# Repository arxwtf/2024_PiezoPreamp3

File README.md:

# Piezo Preamp with Baxandall Tone Control and Battery Indicator

A simple preamp to be used for e.g. guitar piezo (contact) microphones. 

Created in KiCAD v8 and LTSpice.

### [**User manual**](Arx_PiezoPreamp-User_Manual.pdf) | [**Detailed info**](https://arx.wtf/blog/3-piezo-preamp) | [**Enclosure**](https://github.com/arxwtf/2024_PiezoPreamp3_Enclosure)

## Main circuit blocks

### Charge amplifier for piezo 

Basically an integrator circuit. Provides low-impedance input. The gain is adjustable and depends on the input piezo capacitance. In my measurements, piezo discs have following capacitances:

- small disc (15mm diameter): ~7-10nF
- medium disc (27mm diameter): ~16-22nF
- large disc (35mm diameter): ~37-40nF

But I've also seen mentions of piezo discs with <10nF capacitance. Connecting multiple piezo discs in parallel increases the capacitance, so the maximum piezo capacitance can be in order of ~100nF or so.

The gain of the charge amp is then set by the ration of piezo capacitance to charge amp feedback capacitance. The **gain slide switch** is used to select from these feedback capacitances:

- 1nF
- 5.7nF
- 10.4nF
- 23nF

Input is protected by ESD bidirectional diode.

OPA145 is the opamp of choice because of these characteristics:
- JFET input stage, which means low input bias and offset current - critical for a charge amplifier
- low quiescent current (0.7mA max) for battery operation
- acceptable input voltage noise density (7nV/rtHz)
- good current noise density (0.8fA/rtHz)
- sufficient slew rate for audio (20V/us)
- sufficient GBW (5.5MHz)
- single supply voltage range 4.5V - 36V
- output voltage swing (V- +0.3, V+ -0.3)

Opamp also unfortunately seems to have bias current cancellation, which might introduce more current noise - this has to be determined by measurement. The same opamp is also used for Baxandall tone control section. Two single OPA145 components are used instead of dual OPA2145 package because it's easier to route, minimizes crosstalk and improves power dissipation (less heat). This increases the price, of course.

### High-pass filter with HPF switch

The charge amp is followed by a simple first-order high-pass filter with switchable cutoff frequency:
- 0Hz 
- 50Hz
- 77Hz
- 113Hz

The cutoff frequency is selectable by **HPF slide switch**.

### Baxandall tone control with Center switch

Bass and treble can be adjusted independently by **Bass pot** and **Treble pot** in the ranges of +-10dB. The center frequency is switchable by **Center slide switch**:

- 350Hz
- 600Hz
- 1kHz

Output audio is routed through **Volume pot** and protected by ESD bidirectional diode.

### Power-on LED and battery indicator
The power-on LED can work in two modes, switchable by LED mode switch:
- always on (switch left)
- "battery indication mode" (switch right)

**Battery indication mode (BI)** causes the LED to flash briefly when the circuit is switched on (by inserting mono plug to output jack + moving the power-on switch to the right). The longer the flash, the lower the battery voltage (remaining capacity). Under certain threshold, the LED will stay on permanentnly, signalling the need for replacement. This **BI threshold** is adjustable by on-board trimmer pot and needs to be determined by voltmeter measurement.

### Power supply
Designed for 9V batteries or DC pedal power supplies, but should theoretically be able to work properly with up to 18V DC.

Power enters the PCB by means of standardi 5.5/2.1mm DC IN connector with switch to disconnect internal 9V battery.

Contains ESD protection (bidirectional diode), MOSFET reverse polarity protection (with Zener gate protection and CLR) and input pi filter.

### OFF/ON switch with true bypass
The power-on switch works as a true bypass switch in its left position. The device is switched on by moving the switch to the right and insertin a **mono** male audio plug into the output jack.

## Simulation: /ltspice folder
LTSpice simulations (transient, AC, noise, stability) and some graphs are available in `ltspice/` folder.

## /library folder
Folder containing all 3rd symbols, footprints and 3D models used in the project. Other than that, only standard KiCAD symbols are used (opamps, ).

## /production folder
Contains gerbers, position files, BOM file, screenshot of JLC settings etc.

## /resources folder
Contains some additional resources, inspiration and schematics used during development.

## /schematics folder
Contains schematic sheets plotted from KiCAD, individually as .png and in one file as .pdf.

## Known problems
- when the circuit is turned ON or OFF (by the power-on switch and inserting of cable into AUDIO OUT jack), it might produce a strong voltage transient (a loud "pop"). Be careful when you're using it with sensitive equipment downstream.

- battery spring (used only for grounding) is too close to the PCB edge. This creates unnecessary force between the PCB and the enclosure wall. The spring can be shortened, or not used at all.

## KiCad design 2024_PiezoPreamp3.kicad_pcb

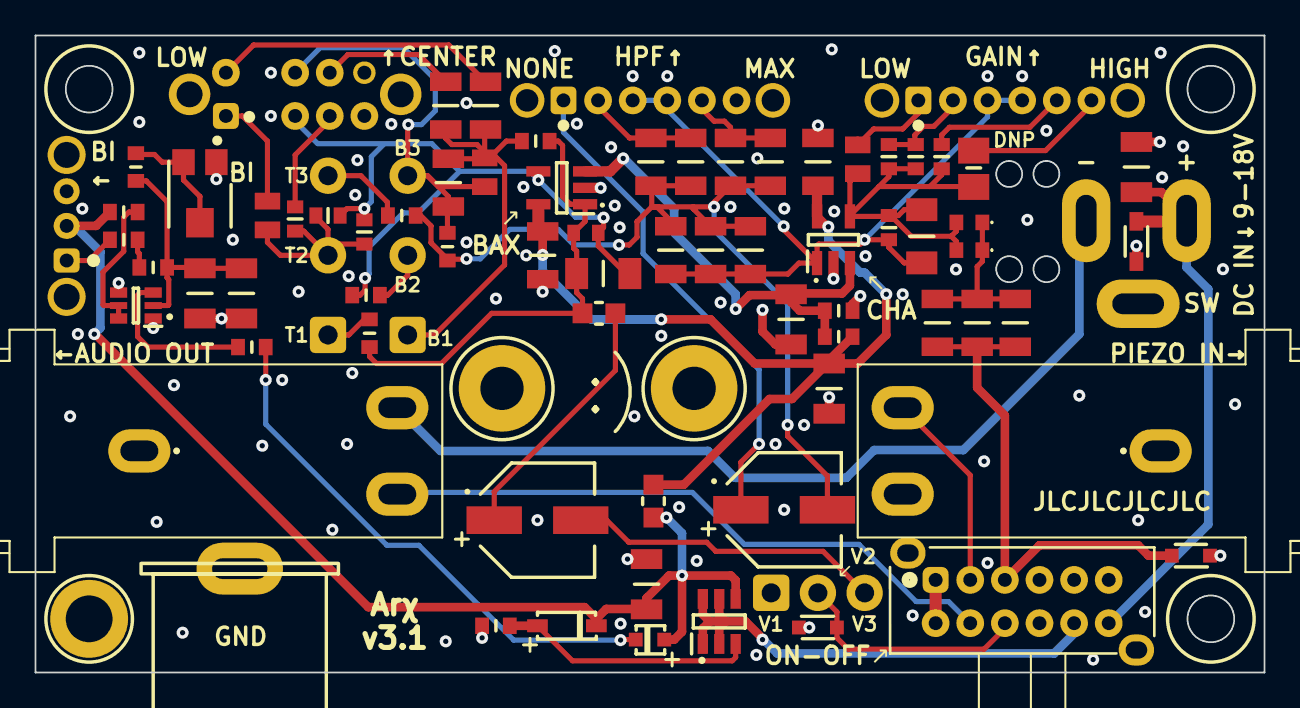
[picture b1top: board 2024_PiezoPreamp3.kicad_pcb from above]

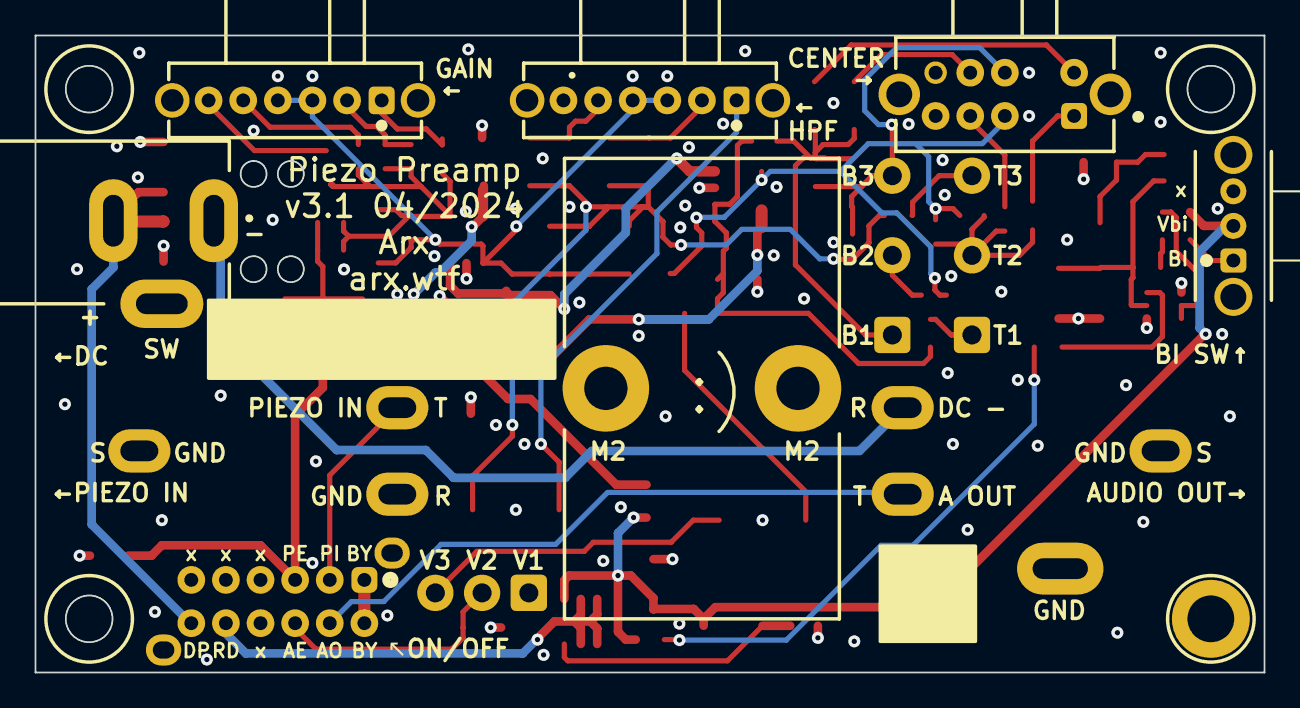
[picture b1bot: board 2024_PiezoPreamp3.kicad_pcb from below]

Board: 4 copper layers, 71.0 x 36.8 mm, 94 parts (6 on the bottom side), 45 nets.

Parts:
Bass: Bass; pot_R16148-1A-1_FabOnly
Batt1, Batt2, Batt3, Batt4: FreeHole_1.5mm
C101, C102, C103: 220n; GRM31C5C1H224JE02L
C104: 100p; cap_CL10C101JB8NNNC
C105: 100u 50V; EEEFTH101XAP
C201, C202, C203, C204, C301, C302: 22u; cap_CL31A226KAHNNNE
C205, C206: 100n; GRM31C5C1H104JA01L
Cb101, Cb104: 68n; GRM31C5C1H683JA01L
Cb102: 22n; GRM21B5C1H223JA01L
Cb103: 100n; GRM31C5C1H104JA01L
Cf101: 1n; GRM1885C1H102JA01D
Cf102: 22n; GRM21B5C1H223JA01L
Cf103, Cf104, Cf105: 4n7; GRM1885C1H472JA01D
Cf106: 1n; cap_SMD_DNP
Chp101, Chp108: 68n; GRM31C5C1H683JA01L
Chp102, Chp103, Chp105, Chp106: 220n; GRM31C5C1H224JE02L
Chp104: 100u 50V; EEEFTH101XAP
Chp107: 100n; GRM31C5C1H104JA01L
Ct101, Ct102, Ct104: 4n7; GRM1885C1H472JA01D
Ct103: 22n; GRM21B5C1H223JA01L
D101, D102: 12V 1pF; CDSOD323-T12LC
D201: 20V 15pF; D20V0L1B2WS-7
D202: DDZ12B-7
D301: Red 100mcd/120°/2mA; APT1608LSECK_J3-PRV
H101: Bass 1; FreePad_1.1mm_2.1mm_rect
H102: Bass 2; FreePad_1.1mm_2.1mm
H103: Bass 3; FreePad_1.1mm_2.1mm
H104: Treble 1; FreePad_1.1mm_2.1mm_rect
H105: Treble 2; FreePad_1.1mm_2.1mm
H106: Treble 3; FreePad_1.1mm_2.1mm
H107: Volume 1; FreePad_1.1mm_2.1mm_rect
H108: Volume 2; FreePad_1.1mm_2.1mm
H109: Volume 3; FreePad_1.1mm_2.1mm
H401: M2.5 MountingHole_Pad; MountingHole_2.7mm_M2.5_ISO14580_Pad
H402, H403, H404: M2.5 MountingHole; MountingHole_2.7mm_M2.5_ISO14580
H422: 9V battery holder; KEYSTONE-71
J101, J102: 6.3mm stereo; CUI_SJ-63053A
J201: DC IN 5.5/2.1mm; 694106301002
J401: Spring Contact; KEYSTONE-5201
R101, R102: 150R; ERA-3AEB151V
R103, R303: 3k9; RT0603FRE073K9L
R104: 10M; MCA1206MD1005BP100
R105, R202: 100R; ERA-6AEB101V
R201, R305: 10k; RT0603BRD0710KL
R203, R204, R301, R302, R304: 47k; RT0603FRD0747KL
RV301: trim B10k; trimpot_TC33X-2-103E
Rb101, Rb102: 3k9; RT0603FRE073K9L
Rf101: 10M; MCA1206MD1005BP100
Rt101, Rt102: 2k2; RT0603DRD072K2L
S101, S102: SK14D01G6; sw_SK14D01G6
S103: 0S203011MA2QP1; sw_0S203011MA2QP1
S201: EG4208A
S301: OS102011MA1QN1
Treble: Treble; pot_R16148-1A-1_FabOnly
U101, U102: OPA145; OPA145IDBVR
U201: ZXMP3A17E6TA
U301: BC847BS,115; bjt_BC847BS_115
Volume: Volume; pot_R16148-1A-1_FabOnly

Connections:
/1-ChargeAmpAndEQ/BASS_1: Cb101.2, Cb102.1, Cb103.2, Cb104.2, H101.1, Rb102.1
/1-ChargeAmpAndEQ/BASS_2: H102.1, R103.1
/1-ChargeAmpAndEQ/BASS_3: Cb101.1, Cb102.2, H103.1, Rb101.2, S103.6 (1_C)
/1-ChargeAmpAndEQ/BAX_A_INV: C104.1, Ct101.1, Ct102.1, R103.2, R104.2, S103.2 (2_C), U102.4 (-)
/1-ChargeAmpAndEQ/BAX_A_OUT: C104.2, R104.1, R105.2, Rb102.2, Rt102.2, U102.1
/1-ChargeAmpAndEQ/BAX_IN: Chp101.2, Chp102.2, Chp103.2, Chp104.2, Chp105.1, Chp106.1, Chp107.2, Chp108.2, Rb101.1, Rt101.1
/1-ChargeAmpAndEQ/CH_A_INV: Cf101.1, Cf102.1, Cf103.1, Cf104.1, Cf105.1, Cf106.1, R101.2, R102.2, Rf101.1, U101.4 (-)
/1-ChargeAmpAndEQ/CH_A_OUT: Cf101.2, Chp101.1, Chp102.1, Chp103.1, Rf101.2, S101.3 (C1), S101.4 (C2), S102.3 (C1), S102.4 (C2), U101.1
/1-ChargeAmpAndEQ/CIN_RIN: C101.2, C102.2, C103.2, R101.1, R102.1
/1-ChargeAmpAndEQ/C_SW_1: Ct103.2, S103.1 (2_1)
/1-ChargeAmpAndEQ/C_SW_2: Ct104.2, S103.3 (2_2)
/1-ChargeAmpAndEQ/C_SW_5: Cb103.1, S103.5 (1_1)
/1-ChargeAmpAndEQ/C_SW_7: Cb104.1, S103.7 (1_2)
/1-ChargeAmpAndEQ/G_SW_1: Cf102.2, S101.1
/1-ChargeAmpAndEQ/G_SW_2: Cf103.2, Cf104.2, S101.2
/1-ChargeAmpAndEQ/G_SW_5: Cf105.2, S101.5 (3)
/1-ChargeAmpAndEQ/G_SW_6: Cf106.2, S101.6 (4)
/1-ChargeAmpAndEQ/HPF_SW_1: Chp104.1, S102.1
/1-ChargeAmpAndEQ/HPF_SW_2: Chp105.2, Chp106.2, S102.2
/1-ChargeAmpAndEQ/HPF_SW_3: Chp107.1, Chp108.1, S102.5 (3)
/1-ChargeAmpAndEQ/ROUT_COUT: C105.1, R105.1
/1-ChargeAmpAndEQ/TREB_1: H104.1, Rt102.1
/1-ChargeAmpAndEQ/TREB_2: Ct101.2, Ct102.2, Ct103.1, Ct104.1, H105.1
/1-ChargeAmpAndEQ/TREB_3: H106.1, Rt101.2
/1-ChargeAmpAndEQ/VOL_3: C105.2, H109.1
/2-Power/BYPASS: S201.1, S201.7
/2-Power/DC_IN_POS: C201.2, D201.2 (A2), J201.2 (SLEEVE), S201.12
/2-Power/RP_DRAIN: S201.11, U201.1, U201.2, U201.5, U201.6
/2-Power/RP_GATE: D202.2 (A), R201.1, U201.3
/3-BatteryIndicator/BI_B1: C301.2, C302.2, R302.2, R303.1, U301.2 (B1)
/3-BatteryIndicator/BI_C1_B2: R304.2, U301.5 (B2), U301.6 (C1)
/3-BatteryIndicator/BI_C2: R305.2, U301.3 (C2)
/3-BatteryIndicator/BI_R: R301.2, R302.1
/3-BatteryIndicator/BI_SW: R301.1, S301.1
/3-BatteryIndicator/LED_K: D301.1 (K), R305.1
/3-BatteryIndicator/TRIM_BI_3: R303.2, RV301.2, RV301.3
AUDIO_ESD: D102.2 (A2), H108.1, S201.9
AUDIO_OUT: J102.2, S201.8
DC_IN_NEG: J102.3, J201.1 (CENTER)
GND: C201.1, C202.1, C203.1, C204.1, C205.1, C206.1, C301.1, C302.1, D101.1 (A1), D102.1 (A1), D201.1 (A1), H107.1, H401.1, J101.1, J101.3, J102.1, J401.1, R201.2, R204.2, RV301.1, U101.2 (V-), U102.2 (V-), U301.1 (E1), U301.4 (E2)
PIEZO_ESD: C101.1, C102.1, C103.1, D101.2 (A2), S201.3
PIEZO_IN: J101.2, S201.2
VS: C203.2, C205.2, C206.2, R202.1, R203.1, U101.5 (V+), U102.5 (V+)
Vbi: C202.2, D202.1 (K), D301.2 (A), R202.2, R304.1, S301.2, U201.4
Vbias: C204.2, R203.2, R204.1, U101.3 (+), U102.3 (+)

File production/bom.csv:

Designator,Footprint,Quantity,Value,LCSC Part #
"C101, C102, C103, Chp102, Chp103, Chp105, Chp106",GRM31C5C1H224JE02L,7,220n,C464977
C104,cap_CL10C101JB8NNNC,1,100p,C14858
"C105, Chp104",EEEFTH101XAP,2,100u 50V,C165974 
"C201, C202, C203, C204, C301, C302",cap_CL31A226KAHNNNE,6,22u,C12891
"C205, C206, Cb103, Chp107",GRM31C5C1H104JA01L,4,100n,C97946
"Cb101, Cb104, Chp101, Chp108",GRM31C5C1H683JA01L,4,68n,C77084
"Cb102, Cf102, Ct103",GRM21B5C1H223JA01L,3,22n,C77069
Cf101,GRM1885C1H102JA01D,1,1n,C77026
"Cf103, Cf104, Cf105, Ct101, Ct102, Ct104",GRM1885C1H472JA01D,6,4n7,C85980
"D101, D102",CDSOD323-T12LC,2,12V 1pF,C911368
D201,D20V0L1B2WS-7,1,20V 15pF,C507921
D202,DDZ12B-7,1,DDZ12B-7,C2760568
D301,APT1608LSECK_J3-PRV,1,Red 100mcd/120°/2mA,C5357909
H422,KEYSTONE-71,1,9V battery holder,-
"J101, J102",CUI_SJ-63053A,2,6.3mm stereo,-
J201,694106301002,1,DC IN 5.5/2.1mm,-
J401,KEYSTONE-5201,1,Spring Contact,-
"R101, R102",ERA-3AEB151V,2,150R,C543626
"R103, R303, Rb101, Rb102",RT0603FRE073K9L,4,3k9,C863790
"R104, Rf101",MCA1206MD1005BP100,2,10M,C4259100
"R105, R202",ERA-6AEB101V,2,100R,C445646
"R201, R305",RT0603BRD0710KL,2,10k,C95204
"R203, R204, R301, R302, R304",RT0603FRD0747KL,5,47k,C728633
RV301,trimpot_TC33X-2-103E,1,trim B10k,C719176
"Rt101, Rt102",RT0603DRD072K2L,2,2k2,C705970
"S101, S102",sw_SK14D01G6,2,SK14D01G6,
S103,sw_0S203011MA2QP1,1,0S203011MA2QP1,
S201,EG4208A,1,EG4208A,-
S301,OS102011MA1QN1,1,OS102011MA1QN1,-
"U101, U102",OPA145IDBVR,2,OPA145,C2058624
U201,ZXMP3A17E6TA,1,ZXMP3A17E6TA,C154715
U301,bjt_BC847BS_115,1,"BC847BS,115",C8653

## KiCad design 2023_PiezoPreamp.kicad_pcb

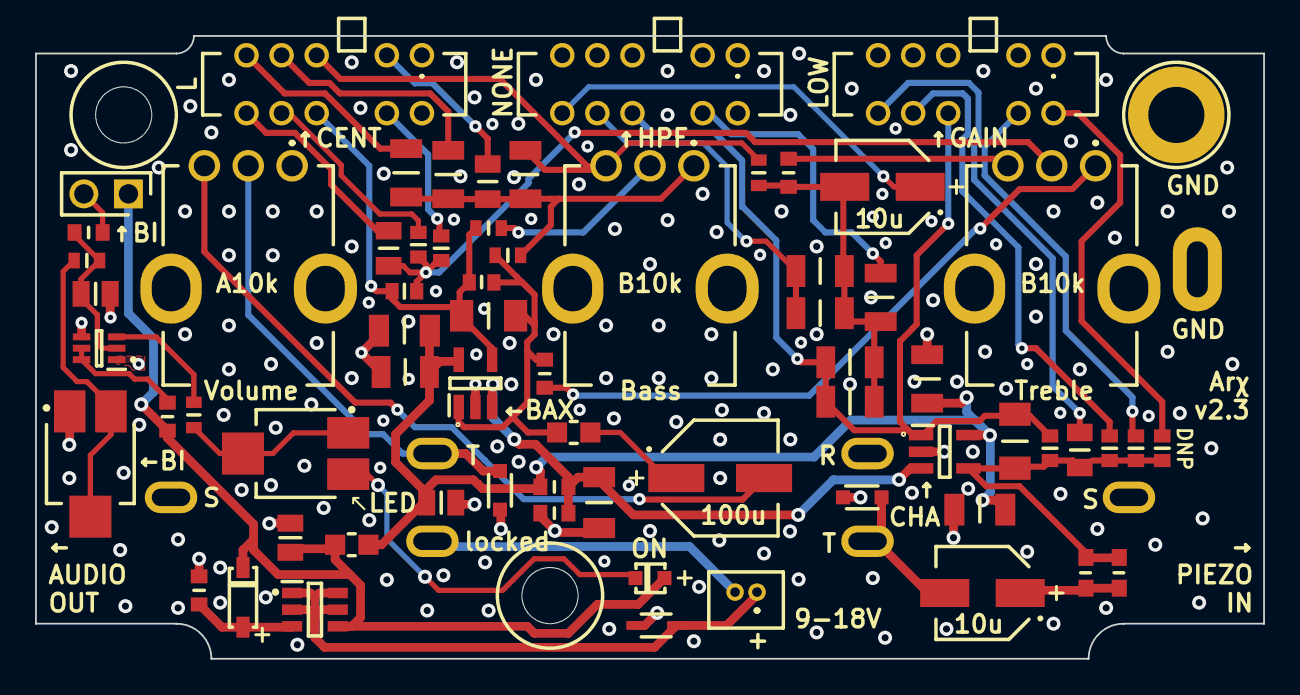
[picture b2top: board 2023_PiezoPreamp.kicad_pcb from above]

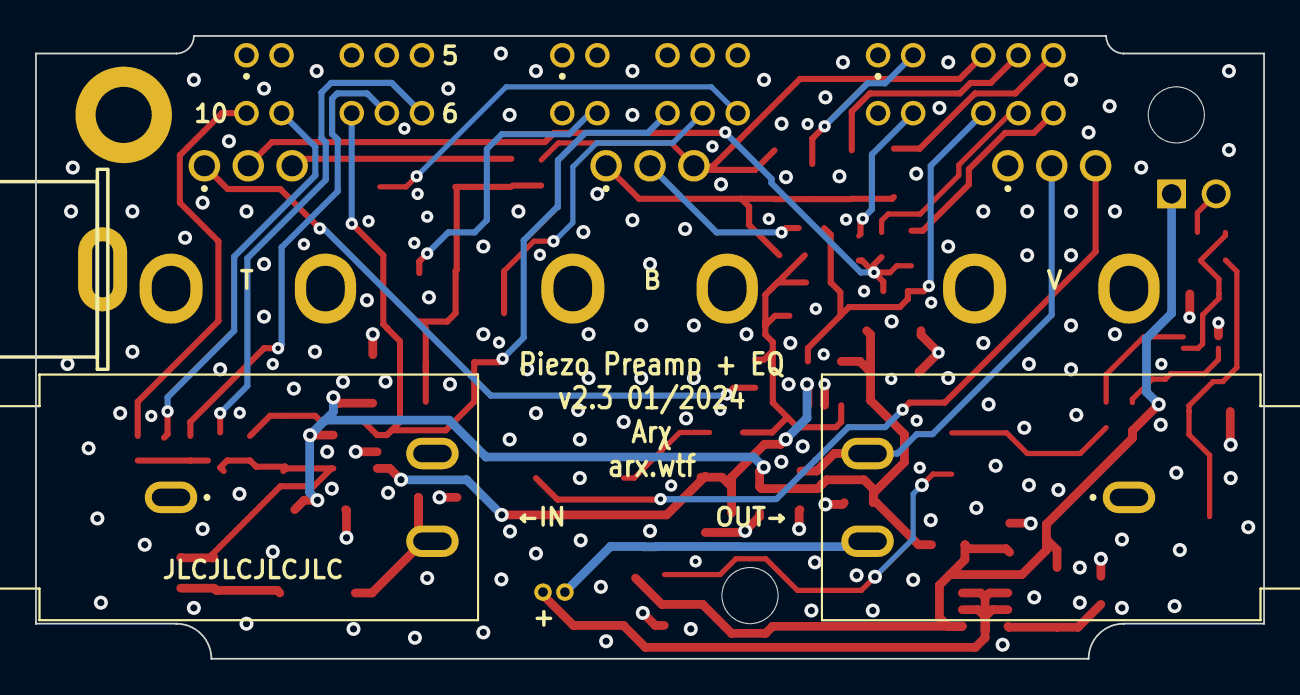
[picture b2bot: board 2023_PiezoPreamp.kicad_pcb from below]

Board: 4 copper layers, 70.0 x 35.5 mm, 73 parts (3 on the bottom side), 43 nets.

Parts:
C101: 10u 50V; EEEFK1H100UR
C102: 100p; GRM1885C1H101JA01D
C103: 100u 50V; EEEFTH101XAP
C201, C202, C301: 22u; GRM21BR61E226ME44L
C203, C205, C207: 10u; C3216X5R1H106K160AB
C204, C206: 100n; GRM31C5C2A104JA01L
Cb101, Cb103: 68n; GRM31C5C1H683JA01L
Cb102: 100n; GRM31C5C2A104JA01L
Cb104: 22n; CGA4J2C0G1H223J125AA
Cf101, Cf105: 1n; GRM1885C1H102JA01D
Cf102: 22n; CGA4J2C0G1H223J125AA
Cf103: 10n; GRM1885C1H103JA01D
Cf104: 4n7; GRM1885C1H472JA01D
Chp101: 68n; GRM31C5C1H683JA01L
Chp102, Chp104, Chp105, Chp106: 220n; GRM31C5C1H224JE02L
Chp103: 10u 50V; EEEFK1H100UR
Ct101, Ct103: 6n8; GRM1885C1H682JA01D
Ct102: 22n; CGA4J2C0G1H223J125AA
Ct104: 4n7; GRM1885C1H472JA01D
D101, D102: 12V 1pF; CDSOD323-T12LC
D201: 20V 15pF; D20V0L1B2WS-7
D202: DDZ12B-7
D301: Red 100mcd/120°/2mA; APT1608LSECK_J3-PRV
H401: M3 MountingHole_Pad; MountingHole_3.2mm_M3_ISO14580_Pad
H402, H403: M3 MountingHole; MountingHole_3.2mm_M3_ISO14580
J101, J102: 6.3mm stereo; CUI_SJ-63053A
J201: Molex PicoBlade; 53047-0210
J301: 2.54mm header; 77311-818-02
J401: Spring Contact; KEYSTONE-5201
R101, R102: 150R; RT0603BRD07150RL_UL-M
R103, R302, R304: 3k9; ERA-3AEB392V
R104: 10M; MCA1206MD1005BP100
R105, R202: 100R; ERA-6AEB101V
R201: 10k; RT0603BRD0710KL
R203, R204, R303: 47k; RT0603BRD0747KL
R301: 100k; RT0603BRD07100KL
RV101, RV102: B10k; PTV09A-4020F-A103
RV103: A10k; PTV09A-4020F-A103
RV301, RV302: trim B10k; ST-4ETB103
Rb101, Rb102: 3k9; ERA-3AEB392V
Rf101: 10M; MCA1206MD1005BP100
Rt101, Rt102: 2k2; RT0603DRD072K2L
S101, S102, S103: SSSS224100
U101, U102: OPA145; OPA145IDBVR
U201: ZXMP3A17E6TA
U301: MMDT2222A-7-F

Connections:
/1-ChargeAmpAndEQ/AUDIO_OUT: D102.2 (A2), J102.2, RV103.2
/1-ChargeAmpAndEQ/BAX_A_INV: C102.1, Ct101.1, R103.2, R104.2, S103.8, U102.4 (-)
/1-ChargeAmpAndEQ/BAX_A_OUT: C102.2, R104.1, R105.2, Rb102.2, Rt102.2, U102.1
/1-ChargeAmpAndEQ/BAX_IN: Chp101.2, Chp102.2, Chp103.2, Chp104.1, Chp105.1, Chp106.1, Rb101.1, Rt101.1
/1-ChargeAmpAndEQ/BA_1: Cb101.1, Cb102.2, Cb103.2, Cb104.2, RV101.1, Rb102.1
/1-ChargeAmpAndEQ/BA_2: R103.1, RV101.2
/1-ChargeAmpAndEQ/BA_3: Cb101.2, RV101.3, Rb101.2, S103.3
/1-ChargeAmpAndEQ/CH_A_INV: Cf101.1, Cf102.1, Cf103.1, Cf104.1, Cf105.1, R101.2, R102.2, Rf101.1, U101.4 (-)
/1-ChargeAmpAndEQ/CH_A_OUT: Cf101.2, Chp101.1, Chp102.1, Rf101.2, S101.8, S102.8, U101.1
/1-ChargeAmpAndEQ/CIN_RIN: C101.1, R101.1, R102.1
/1-ChargeAmpAndEQ/C_SW_2: Cb104.1, S103.2
/1-ChargeAmpAndEQ/C_SW_4: Cb103.1, S103.4
/1-ChargeAmpAndEQ/C_SW_5: Cb102.1, S103.5
/1-ChargeAmpAndEQ/C_SW_6: Ct102.2, S103.6
/1-ChargeAmpAndEQ/C_SW_7: Ct103.2, S103.7
/1-ChargeAmpAndEQ/C_SW_9: Ct104.2, S103.9
/1-ChargeAmpAndEQ/G_SW_6: Cf102.2, S101.6
/1-ChargeAmpAndEQ/G_SW_7: Cf103.2, S101.7
/1-ChargeAmpAndEQ/G_SW_9: Cf104.2, S101.9
/1-ChargeAmpAndEQ/G_SW_10: Cf105.2, S101.10
/1-ChargeAmpAndEQ/HPF_SW_6: Chp103.1, S102.6
/1-ChargeAmpAndEQ/HPF_SW_7: Chp104.2, Chp105.2, S102.7
/1-ChargeAmpAndEQ/HPF_SW_9: Chp106.2, S102.9
/1-ChargeAmpAndEQ/PIEZO_IN: C101.2, D101.2 (A2), J101.2
/1-ChargeAmpAndEQ/ROUT_COUT: C103.1, R105.1
/1-ChargeAmpAndEQ/TR_1: RV102.1, Rt102.1
/1-ChargeAmpAndEQ/TR_2: Ct101.2, Ct102.1, Ct103.1, Ct104.1, RV102.2
/1-ChargeAmpAndEQ/TR_3: RV102.3, Rt101.2
/1-ChargeAmpAndEQ/VOL_3: C103.2, RV103.3
/2-Power/DC_IN_POS: D201.2 (A2), J201.1, U201.1, U201.2, U201.5, U201.6
/2-Power/RP_GATE: D202.2 (A), R201.1, U201.3
/3-BatteryIndicator/BI_B1: R303.2, U301.5 (B1), U301.6 (C2)
/3-BatteryIndicator/BI_B2: C301.2, R301.2, R302.1, U301.2 (B2)
/3-BatteryIndicator/BI_C1: R304.2, U301.3 (C1)
/3-BatteryIndicator/BI_SW: J301.2, R301.1
/3-BatteryIndicator/LED_K: D301.1 (K), RV302.3
/3-BatteryIndicator/TRIM_BI_3: R302.2, RV301.2, RV301.3
/3-BatteryIndicator/TRIM_LED_1: R304.1, RV302.1, RV302.2
DC_IN_NEG: J102.3, J201.2
GND: C201.1, C202.1, C203.1, C204.1, C205.1, C206.1, C207.1, C301.1, D101.1 (A1), D102.1 (A1), D201.1 (A1), H401.1, J101.1, J101.3, J102.1, J401.1, R201.2, R204.2, RV103.1, RV301.1, U101.2 (V-), U102.2 (V-), U301.1 (E2), U301.4 (E1)
VS: C202.2, C204.2, C205.2, C206.2, C207.2, R202.1, R203.1, U101.5 (V+), U102.5 (V+)
Vbi: C201.2, D202.1 (K), D301.2 (A), J301.1, R202.2, R303.1, U201.4
Vbias: C203.2, R203.2, R204.1, U101.3 (+), U102.3 (+)

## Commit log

2023-12-07 adding README
2023-12-07 adding .gitignore - first version
2023-12-07 updated gitignore
2023-12-07 adding main project files and symbol/footprint/3d model library
2023-12-07 adding LTSpice simulations
2023-12-07 adding resources/ folder
2023-12-07 updating .gitignore - adding lockfile
2023-12-07 updating gitignore - adding PCB lockfile as well
2023-12-07 resolving all violations of stitching vias
2023-12-07 removing forggoten text
2023-12-07 final touches to footprints
2023-12-07 final touches to board and schematic before manufacture / assembly
2023-12-07 generating production files: gerbers, drill files, positions, BOM for assembly
2023-12-08 bumping revision number to v2.1
2023-12-08 fixing some of 0805 and 1206 land patterns so that they have enough soldering area (after JLC feedback)
2023-12-08 fixing footprints - making pin 1 dots more prominent, adding + signs to caps and diodes
2023-12-08 PCB: few minor fixes, vias etc
2023-12-08 v2.1: new production gerbers
2023-12-08 v2.1: new production assembly files
2023-12-08 new production gerbers (still v2.1, correcting silkscreen mistake)
2023-12-08 updating the project and board (silkscreen mistake, was v2.0 instead of v2.1)
2023-12-27 v2.2: correcting pins of audio jacks - T and R were swapped. Fixing in schematic and PCB
2023-12-27 v2.2: new production files (gerbers, drills, positions, bom)
2024-01-09 renaming production files folder
2024-01-09 updating DRC exclusions
2024-01-10 adding folder with plotted schematics and rendered final PCB
2024-01-10 plotted schematics: replacing .svg files with .png
2024-01-10 Updated README.md, added rendered PCB image
2024-01-10 Updating README.md - adding "Known problems" section
2024-01-17 v2.3: adjusting board dimensions to better fit Teko 1/A.1 enclosure. Increasing pad sizes for opamps and 10M resistors to make hand soldering easier.
2024-01-17 production files for v2.3
2024-01-17 updating rendered board image
2024-02-01 LTSpice: trying to make the simulations little less dependent on my library by including .asy files for TVS diodes. Also trying to simulate EOS, but it's unclear
2024-02-01 Schematic: improving comments about ESD protection
2024-02-11 library: adding new symbols and footprints
2024-02-11 library: improving existing symbols and footprints
2024-02-11 improving the schematic - v3.0. Very crude draft of board layout with battery holder underneath the PCB
2024-02-11 ltspice: improving stability simulation
2024-02-11 trying out board cutout, rough draft
2024-02-11 second attempt at component placement
2024-02-12 improving 9V battery holder 3D model
2024-02-12 library: improving switch and pot models, adding new cap models
2024-02-12 working on component placement, improving schematics
2024-02-12 saving in Kicad8 for the first time - some underlying formats changed
2024-02-12 saving PCB in kicad 8 format
2024-02-15 LTSpice: simulating Battery Indicator circuit
2024-02-15 library: cleaning up, adding new footprints and models, moving old unused footprints to old/ folder
2024-02-15 LTSpice: BI simulation now uses BC847B BJT
2024-02-15 ltspice: removing spaces from all names
2024-02-15 removing unused libs from sym-lib-table
2024-02-15 schematics: heavy BOM optimization, many small changes, filling missing fields, improving symbols and everything
2024-02-15 PCB: updating footprints from schematic
2024-02-15 library: improving symbols
2024-02-15 aligning schematics to grid, swapping switches as they are on the bottom side now; rough placement of BI section on board
2024-02-18 library: replacing G, LPF and C switches with three different swiches. moving unused things around
2024-02-18 schematics: replacing the switches, rewiring, improving center switch positions, removing 6n8 cap
2024-02-18 LTSpice: reflecting recent changes in simulations
2024-02-18 PCB: updating all component footprints from schematics; starting some basic placement again
2024-02-20 schematic: renaming low-pass filter to high-pass filter as it was named incorrectly lol
2024-02-20 updating the board and remaining low-pass references in schematic
2024-02-20 Schematic: replacing SP3T HPF switch with SP4T again, adding the new HPF cutoff position, moving libraries around. Choosing different 150R resistor because of availability
2024-02-20 LTSpice: updating HPF values
2024-02-20 LTSpice: updating HPF values in stability simulation as well
2024-02-22 Update README.md - correcting filter name
2024-02-22 fixing missing DC jack; continued working on the board layout
2024-02-22 correcting the filter name to HPF in schematic, board and in exported schematics
2024-02-22 updating rendered PCB image
2024-02-22 v2.3: new production outputs
2024-02-22 updating DRC exclusions list
2024-02-22 renaming the project from 2023_PiezoPreamp
2024-02-23 library: updating some silkscreens etc
2024-02-23 library: adding standoffs
2024-02-23 schematic: finishing standoffs, screws, minor improvements
2024-02-23 PCB: mainly placing and improving silkscreen
2024-02-23 Schematic: adding 9V battery clip
2024-02-24 PCB: minor improvements
2024-03-04 Schematics: improving Purpose of some components
2024-03-05 PCB: layout, routing
2024-03-05 schematic, PCB: defining net classes, assigning different color for Power, getting rid of 0.3493 trace width which was kinda silly anyway
2024-03-05 PCB: changing all via sizes to 0.3/0.7 as bigger don't make any sense
2024-03-05 PCB: making all power traces 0.4mm wide as 0.5mm is excessive
2024-03-05 PCB: layouting, routing
2024-03-07 Schematic, PCB: moving DC ESD protection in front of the switch. Using one 22uF bulk decoupling cap where DC enters the board instead of two 10uF near opamps. Using 22uF instead of 10uF in opamp bias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
2024-03-07 schematic: graphical improvements
2024-03-07 PCB: changing power traces to 0.5mm width again. I have enough space and the inductance is lower
2024-03-07 PCB: enlarging all the pads that will be manually soldered
2024-03-08 Using larger footprint for DNP feedback cap; small improvements
2024-03-10 library: optimizing few components, moving the old ones, improving silkscreens and such
2024-03-10 schematic: optimizing few BOM items (for less costly alternatives), few updates
2024-03-10 project: defining fields and symbol table views
2024-03-10 PCB: finishing layout & routing, improving silkscreen everywhere, checking rules
2024-03-11 PCB: moving tracks & vias so that the signals don't cross holes in gnd planes cause by signal vias
2024-03-11 PCB: stitching vias
2024-03-11 PCB: improving track aesthetics, some vias, zone corners. Setting plot outputs closer to JLC recommendation
2024-03-11 removing v2 gerber archives
2024-03-11 schematic: adding on/off sw datasheet
2024-03-11 PCB, library: minor improvements after gerber inspection
2024-03-11 PCB: updating sheet info
2024-03-11 PCB: locking all footprints, text and graphics. Excluding THT from BOM for fabrication purposes
2024-03-11 PCB: adding free holes for battery jack cables. Moving things around a bit
2024-03-12 removing old v2 production files
2024-03-12 PCB: adjusting silkscreen, do not tent vias
2024-03-12 removing old gerbers folder
2024-03-12 PCB: updating fields from schematic
2024-03-12 schematic, PCB: many small adjustments before fab&assembly
2024-03-12 updating gitignore
2024-03-13 production files sent to prototype assembly
2024-03-13 deleting old v2 leftovers from merge
2024-03-13 PCB: adjusting User.Drawings texts
2024-03-13 PCB: improving user.drawings
2024-04-07 adjusting user drawings
2024-04-08 library: marking THT components as 'excluded from position files' as otherwise kicad would bug me with 'doesnt match library' warnings forever
2024-04-08 PCB: v3.1 - small adjustments to DC IN jack footprint, DC ESD footprint, moving things a little, increasing S/N field size, etc
2024-04-08 schematic: increasing version to 3.1
2024-04-08 v3.1: production files, backing up v3.0
2024-04-08 removing old v2.3 production gerbers
2024-04-08 adding production settings for JLCPCB
2024-04-23 updating README, render, small things in schematics and pcb
2024-04-23 trying webp format for schematic image
2024-04-23 updating schematics exports (just the images). replacing the .png version with .webp
2025-01-11 LTSpice: improving circuits, plots, adding more screenshots
2025-01-11 improving README
2025-01-11 Schematics: improving a few comments and their positions
2025-01-11 updating schematics exports
2025-01-11 adding User Manual
2025-01-11 updating README
